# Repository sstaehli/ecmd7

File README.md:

# ECMD7

3-Phase Power Converter Hardware for Motor Drive Experiments.

Check the [documentation pages on gitlab.airhead.ch](https://gitlab-pages.airhead.ch/products/arnimatic/ecmd7/) or [documentation pages on GitHub](https://sstaehli.github.io/ecmd7/) for more info.

[](
https://github.com/sstaehli/ecmd7/actions/workflows/ci.yml
)

[](
https://gitlab.airhead.ch/products/arnimatic/ecmd7/-/pipelines
)

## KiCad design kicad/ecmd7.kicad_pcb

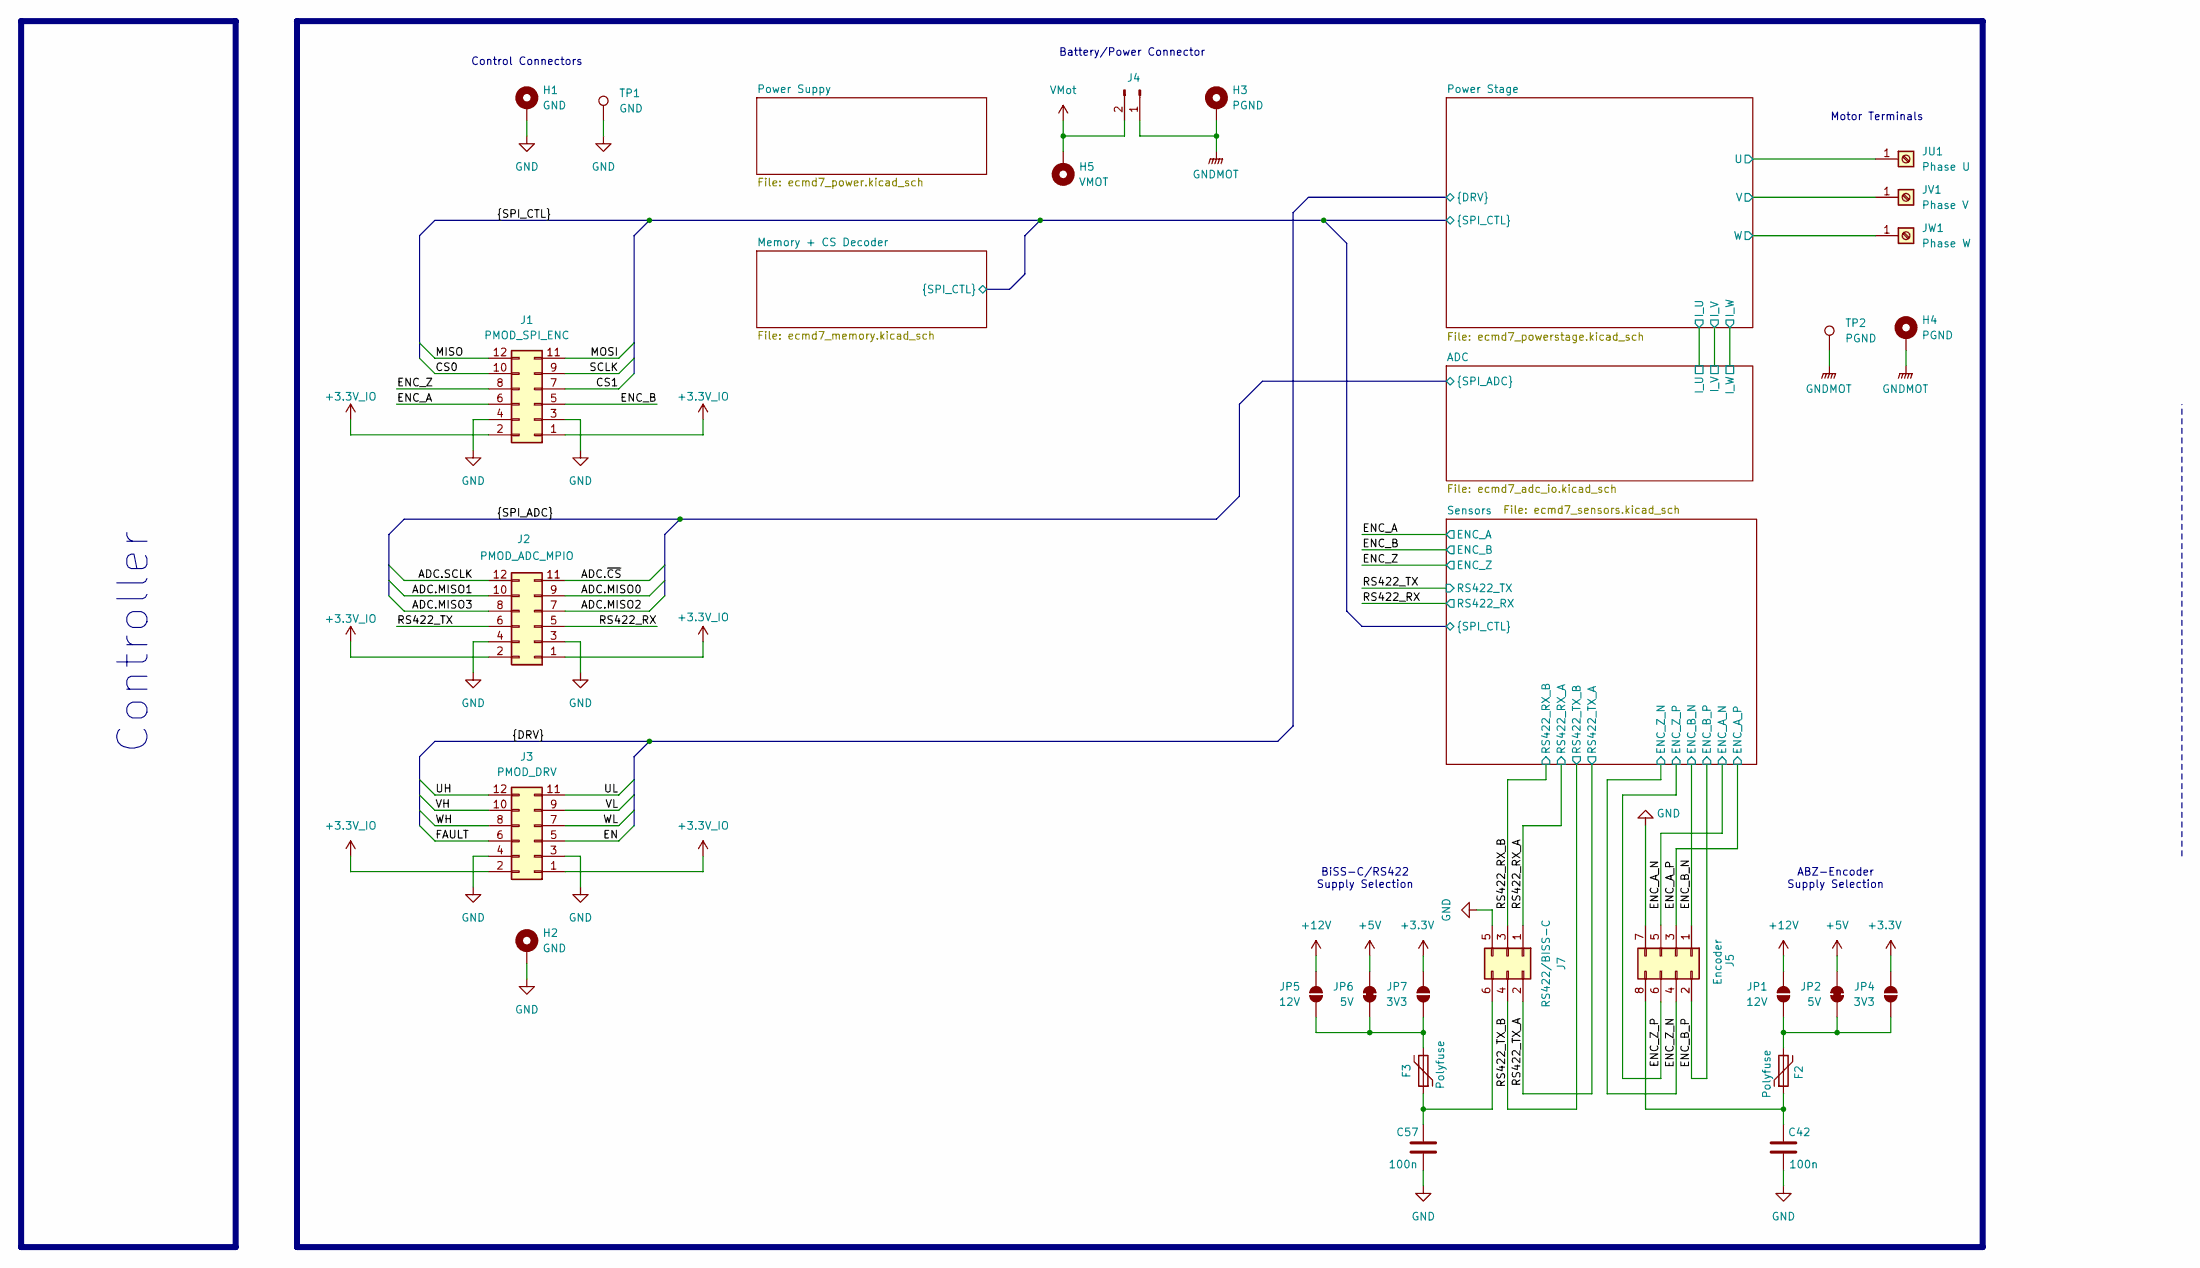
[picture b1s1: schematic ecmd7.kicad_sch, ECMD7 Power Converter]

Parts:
C42, C57: 100n; C_0805_2012Metric
F2, F3: Polyfuse; Fuse_0805_2012Metric
H1, H2: GND; MountingHole_3.2mm_M3_Pad_Via
H3, H4: PGND; MountingHole_3.2mm_M3_Pad_Via
H5: VMOT; MountingHole_3.2mm_M3_Pad_Via
J1: PMOD_SPI_ENC; PinHeader_2x06_P2.54mm_Horizontal
J2: PMOD_ADC_MPIO; PinHeader_2x06_P2.54mm_Horizontal
J3: PMOD_DRV; PinHeader_2x06_P2.54mm_Horizontal
J4: Conn_01x02_Socket; AMASS_XT60-M_1x02_P7.20mm_Vertical
J5: Encoder; PinHeader_2x04_P2.54mm_Vertical
J7: RS422/BISS-C; PinHeader_2x03_P2.54mm_Vertical
JP1, JP5: 12V; SolderJumper-2_P1.3mm_Open_RoundedPad1.0x1.5mm
JP2, JP6: 5V; SolderJumper-2_P1.3mm_Bridged_RoundedPad1.0x1.5mm
JP4, JP7: 3V3; SolderJumper-2_P1.3mm_Open_RoundedPad1.0x1.5mm
JU1: Phase U; MountingHole_3.2mm_M3_Pad_Via
JV1: Phase V; MountingHole_3.2mm_M3_Pad_Via
JW1: Phase W; MountingHole_3.2mm_M3_Pad_Via
TP1: GND; TestPoint_Loop_D2.50mm_Drill1.0mm
TP2: PGND; TestPoint_Loop_D2.50mm_Drill1.0mm

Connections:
+3.3V: JP4.2 (B), JP7.2 (B); also elsewhere on the board
+3.3V_IO: J1.1, J1.2, J2.1, J2.2, J3.1, J3.2; also elsewhere on the board
+5V: JP2.2 (B), JP6.2 (B); also elsewhere on the board
+12V: JP1.2 (B), JP5.2 (B); also elsewhere on the board
/ADC.MISO0: J2.9; also elsewhere on the board
/ADC.MISO1: J2.10; also elsewhere on the board
/ADC.MISO2: J2.7; also elsewhere on the board
/ADC.MISO3: J2.8; also elsewhere on the board
/ADC.SCLK: J2.12; also elsewhere on the board
/ADC.~CS: J2.11; also elsewhere on the board
/CS0: J1.10; also elsewhere on the board
/CS1: J1.7; also elsewhere on the board
/EN: J3.5; also elsewhere on the board
/ENC_A: J1.6; also elsewhere on the board
/ENC_A_N: J5.5; also elsewhere on the board
/ENC_A_P: J5.3; also elsewhere on the board
/ENC_B: J1.5; also elsewhere on the board
/ENC_B_N: J5.1; also elsewhere on the board
/ENC_B_P: J5.2; also elsewhere on the board
/ENC_Z: J1.8; also elsewhere on the board
/ENC_Z_N: J5.4; also elsewhere on the board
/ENC_Z_P: J5.6; also elsewhere on the board
/FAULT: J3.6; also elsewhere on the board
/MISO: J1.12; also elsewhere on the board
/MOSI: J1.11; also elsewhere on the board
/Power Stage/U: JU1.1; also elsewhere on the board
/Power Stage/V: JV1.1; also elsewhere on the board
/Power Stage/W: JW1.1; also elsewhere on the board
/RS422_RX: J2.5; also elsewhere on the board
/RS422_RX_A: J7.1; also elsewhere on the board
/RS422_RX_B: J7.3; also elsewhere on the board
/RS422_TX: J2.6; also elsewhere on the board
/RS422_TX_A: J7.2; also elsewhere on the board
/RS422_TX_B: J7.4; also elsewhere on the board
/SCLK: J1.9; also elsewhere on the board
/UH: J3.12; also elsewhere on the board
/UL: J3.11; also elsewhere on the board
/VH: J3.10; also elsewhere on the board
/VL: J3.9; also elsewhere on the board
/WH: J3.8; also elsewhere on the board
/WL: J3.7; also elsewhere on the board
GND: C42.2, C57.2, H1.1, H2.1, J1.3, J1.4, J2.3, J2.4, J3.3, J3.4, J5.7, J7.5, TP1.1; also elsewhere on the board
GNDMOT: H3.1, H4.1, J4.1, TP2.1; also elsewhere on the board
unnamed: C42.1, F2.1, J5.8
unnamed: C57.1, F3.1, J7.6
unnamed: F2.2, JP1.1 (A), JP2.1 (A), JP4.1 (A)
unnamed: F3.2, JP5.1 (A), JP6.1 (A), JP7.1 (A)
VMot: H5.1, J4.2; also elsewhere on the board

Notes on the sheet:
ABZ-Encoder Supply Selection
Controller
Battery/Power Connector
Motor Terminals
Control Connectors
BiSS-C/RS422 Supply Selection

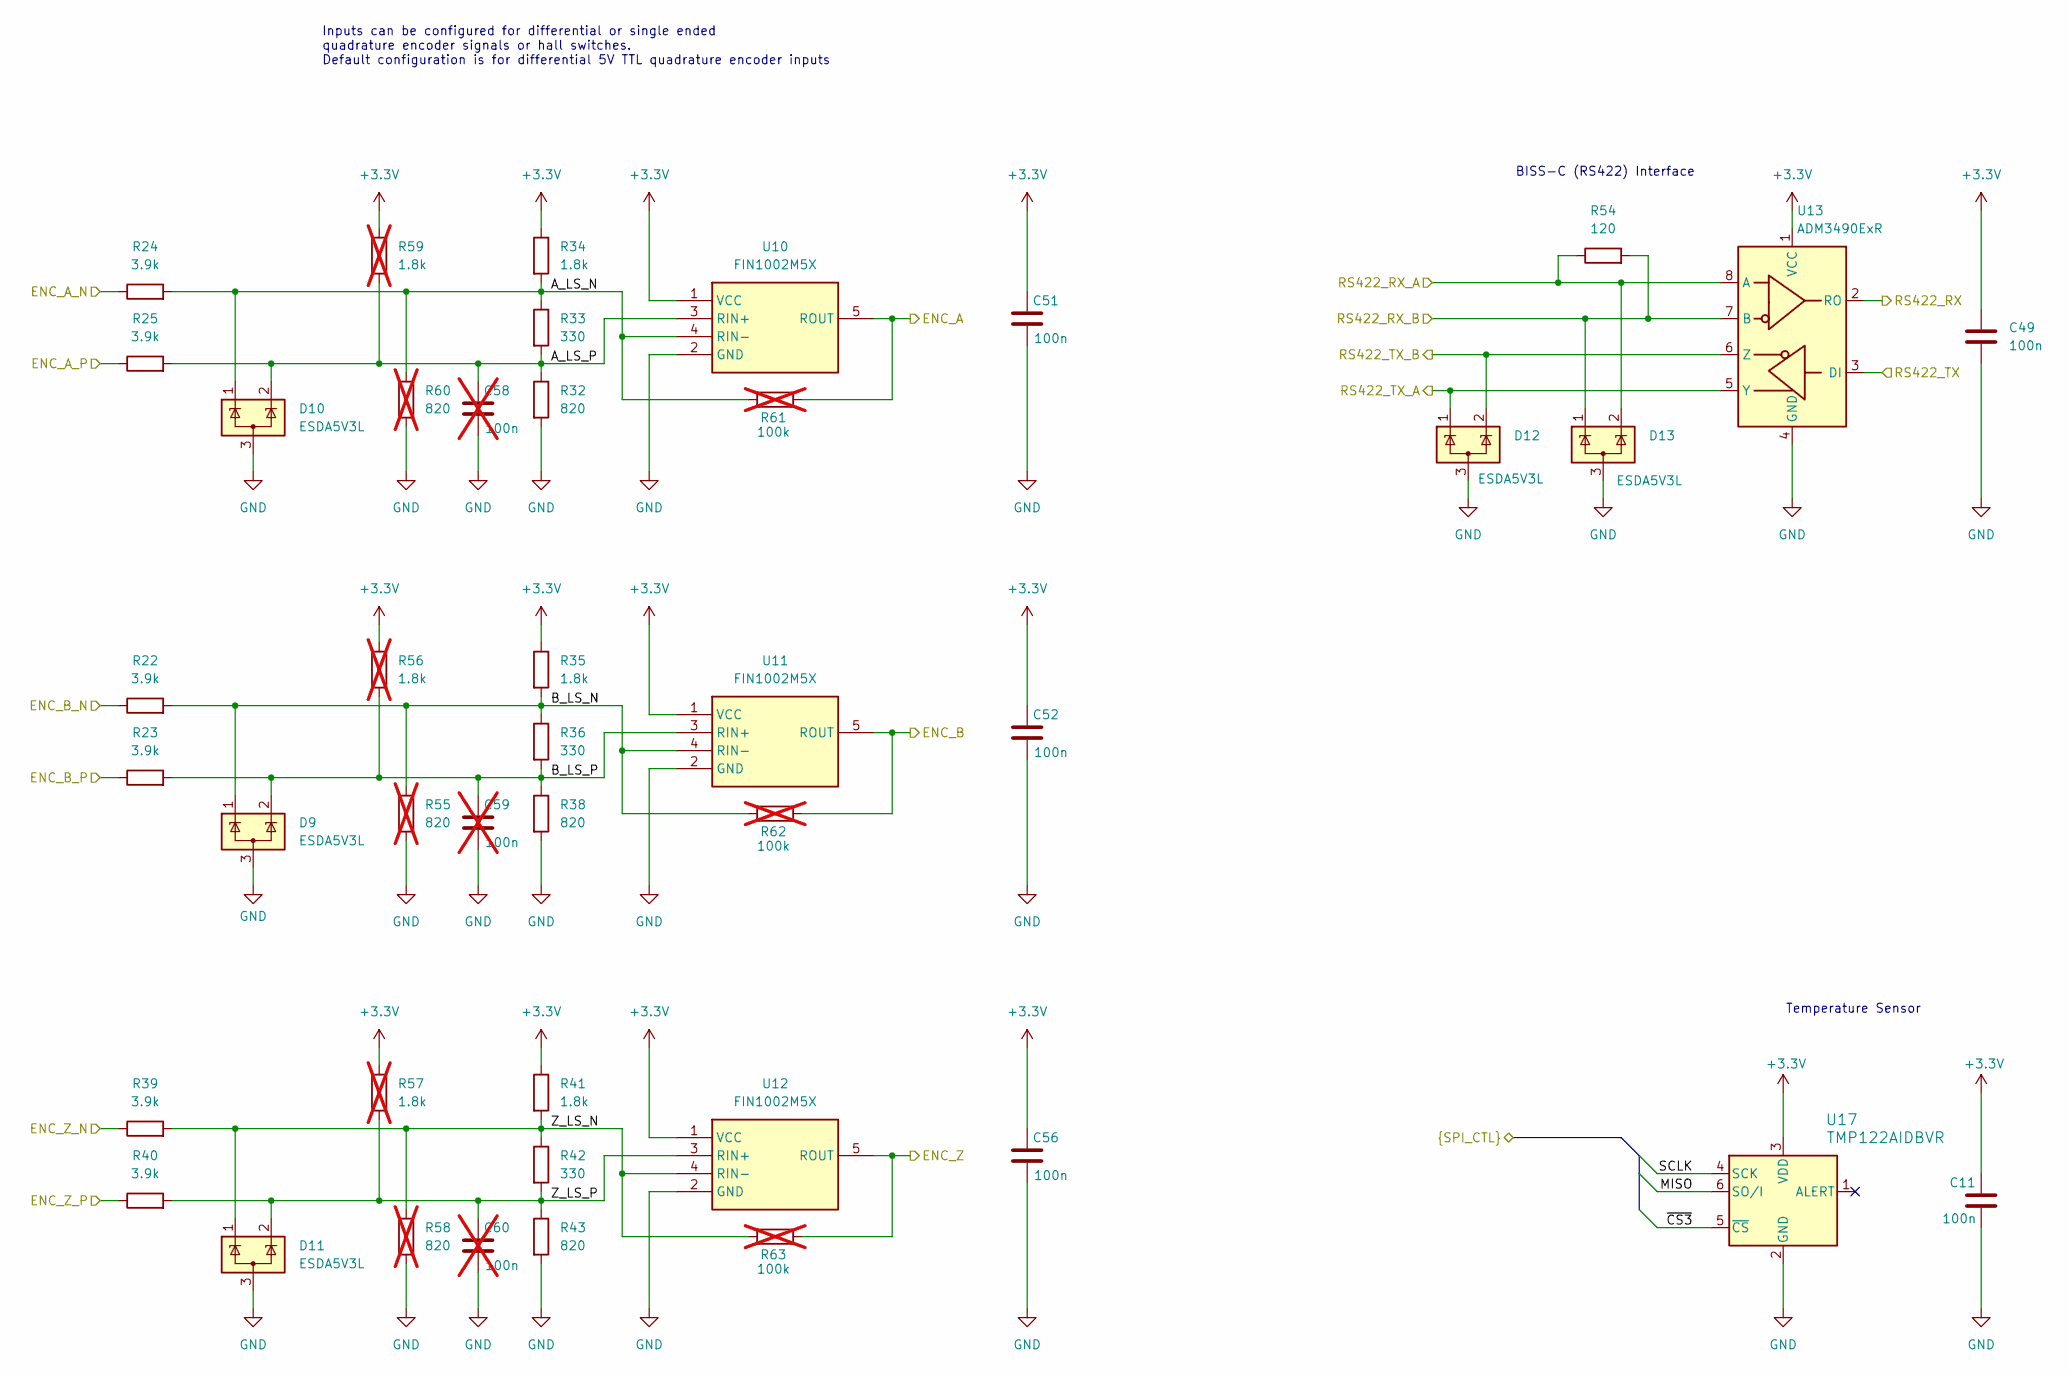
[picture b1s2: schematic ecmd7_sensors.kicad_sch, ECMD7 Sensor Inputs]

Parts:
C11, C51, C52, C56: 100n; C_0805_2012Metric
C49: 100n; C_0603_1608Metric; Mouser Part Number 581-06035C104KAT2A
C58, C59, C60: 100n; C_0805_2012Metric; not fitted
D9, D10, D11, D12, D13: ESDA5V3L; SOT-23-3; Mouser Part Number 511-ESDA5V3L
R22, R23, R24, R25, R39, R40: 3.9k; R_0805_2012Metric
R32, R38, R43: 820; R_0805_2012Metric
R33, R36, R42: 330; R_0805_2012Metric
R34, R35, R41: 1.8k; R_0805_2012Metric
R54: 120; R_0805_2012Metric
R55, R58, R60: 820; R_0805_2012Metric; not fitted
R56, R57, R59: 1.8k; R_0805_2012Metric; not fitted
R61, R62, R63: 100k; R_0805_2012Metric; not fitted
U10, U11, U12: FIN1002M5X; SOT-23-5; Mouser Part Number 512-FIN1002M5X
U13: ADM3490ExR; SOIC-8_3.9x4.9mm_P1.27mm; Mouser Part Number 584-ADM3490EARZ
U17: TMP122AIDBVR; DBV6

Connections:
+3.3V: C11.1, C49.1, C51.1, C52.1, C56.1, R34.1, R35.1, R41.1, R56.1, R57.1, R59.1, U10.1 (VCC), U11.1 (VCC), U12.1 (VCC), U13.1 (VCC), U17.3 (VDD); also elsewhere on the board
/ENC_A: R61.2, U10.5 (ROUT); also elsewhere on the board
/ENC_A_N: R24.1; also elsewhere on the board
/ENC_A_P: R25.1; also elsewhere on the board
/ENC_B: R62.2, U11.5 (ROUT); also elsewhere on the board
/ENC_B_N: R22.1; also elsewhere on the board
/ENC_B_P: R23.1; also elsewhere on the board
/ENC_Z: R63.2, U12.5 (ROUT); also elsewhere on the board
/ENC_Z_N: R39.1; also elsewhere on the board
/ENC_Z_P: R40.1; also elsewhere on the board
/MISO: U17.6 (SO/I); also elsewhere on the board
/RS422_RX: U13.2 (RO); also elsewhere on the board
/RS422_RX_A: D13.2 (K), R54.1, U13.8 (A); also elsewhere on the board
/RS422_RX_B: D13.1 (K), R54.2, U13.7 (B); also elsewhere on the board
/RS422_TX: U13.3 (DI); also elsewhere on the board
/RS422_TX_A: D12.1 (K), U13.5 (Y); also elsewhere on the board
/RS422_TX_B: D12.2 (K), U13.6 (Z); also elsewhere on the board
/SCLK: U17.4 (SCK); also elsewhere on the board
/Sensors/A_LS_N: D10.1 (K), R24.2, R33.1, R34.2, R60.1, R61.1, U10.4 (RIN-)
/Sensors/A_LS_P: C58.1, D10.2 (K), R25.2, R32.1, R33.2, R59.2, U10.3 (RIN+)
/Sensors/B_LS_N: D9.1 (K), R22.2, R35.2, R36.1, R55.1, R62.1, U11.4 (RIN-)
/Sensors/B_LS_P: C59.1, D9.2 (K), R23.2, R36.2, R38.1, R56.2, U11.3 (RIN+)
/Sensors/Z_LS_N: D11.1 (K), R39.2, R41.2, R42.1, R58.1, R63.1, U12.4 (RIN-)
/Sensors/Z_LS_P: C60.1, D11.2 (K), R40.2, R42.2, R43.1, R57.2, U12.3 (RIN+)
/~CS3: U17.5 (~CS); also elsewhere on the board
GND: C11.2, C49.2, C51.2, C52.2, C56.2, C58.2, C59.2, C60.2, D9.3 (A), D10.3 (A), D11.3 (A), D12.3 (A), D13.3 (A), R32.2, R38.2, R43.2, R55.2, R58.2, R60.2, U10.2 (GND), U11.2 (GND), U12.2 (GND), U13.4 (GND), U17.2 (GND); also elsewhere on the board

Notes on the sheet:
Temperature Sensor
Inputs can be configured for differential or single ended quadrature encoder signals or hall switches. Default configuration is for differential 5V TTL quadrature encoder inputs
BISS-C (RS422) Interface

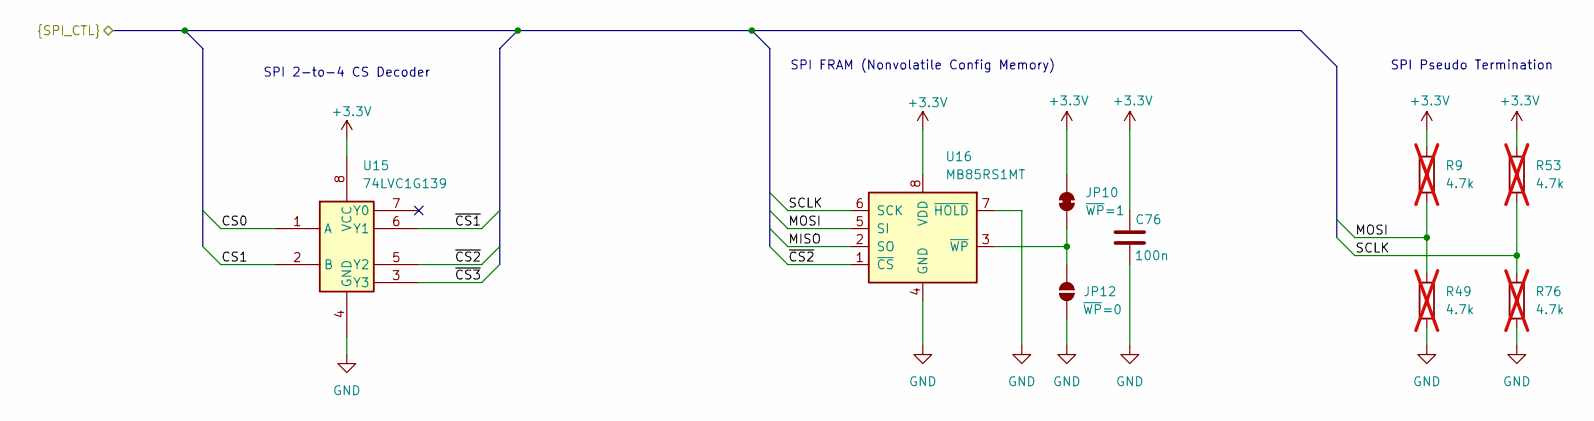
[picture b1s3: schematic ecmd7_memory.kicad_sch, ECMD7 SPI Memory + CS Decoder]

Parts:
C76: 100n; C_0805_2012Metric
JP10: ~{WP}=1; SolderJumper-2_P1.3mm_Bridged_RoundedPad1.0x1.5mm
JP12: ~{WP}=0; SolderJumper-2_P1.3mm_Open_RoundedPad1.0x1.5mm
R9, R49, R53, R76: 4.7k; R_0805_2012Metric; not fitted
U15: 74LVC1G139; SSOP-8_2.95x2.8mm_P0.65mm
U16: MB85RS1MT; SOP-8_3.76x4.96mm_P1.27mm

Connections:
+3.3V: C76.1, JP10.2 (B), R9.1, R53.1, U15.8 (VCC), U16.8 (VDD); also elsewhere on the board
/CS0: U15.1 (A); also elsewhere on the board
/CS1: U15.2 (B); also elsewhere on the board
/MISO: U16.2 (SO); also elsewhere on the board
/MOSI: R9.2, R49.1, U16.5 (SI); also elsewhere on the board
/SCLK: R53.2, R76.1, U16.6 (SCK); also elsewhere on the board
/~CS1: U15.6 (Y1); also elsewhere on the board
/~CS2: U15.5 (Y2), U16.1 (~CS)
/~CS3: U15.3 (Y3); also elsewhere on the board
GND: C76.2, JP12.1 (A), R49.2, R76.2, U15.4 (GND), U16.4 (GND), U16.7 (~HOLD); also elsewhere on the board
unnamed: JP10.1 (A), JP12.2 (B), U16.3 (~WP)

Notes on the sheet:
SPI 2-to-4 CS Decoder
SPI Pseudo Termination
SPI FRAM (Nonvolatile Config Memory)

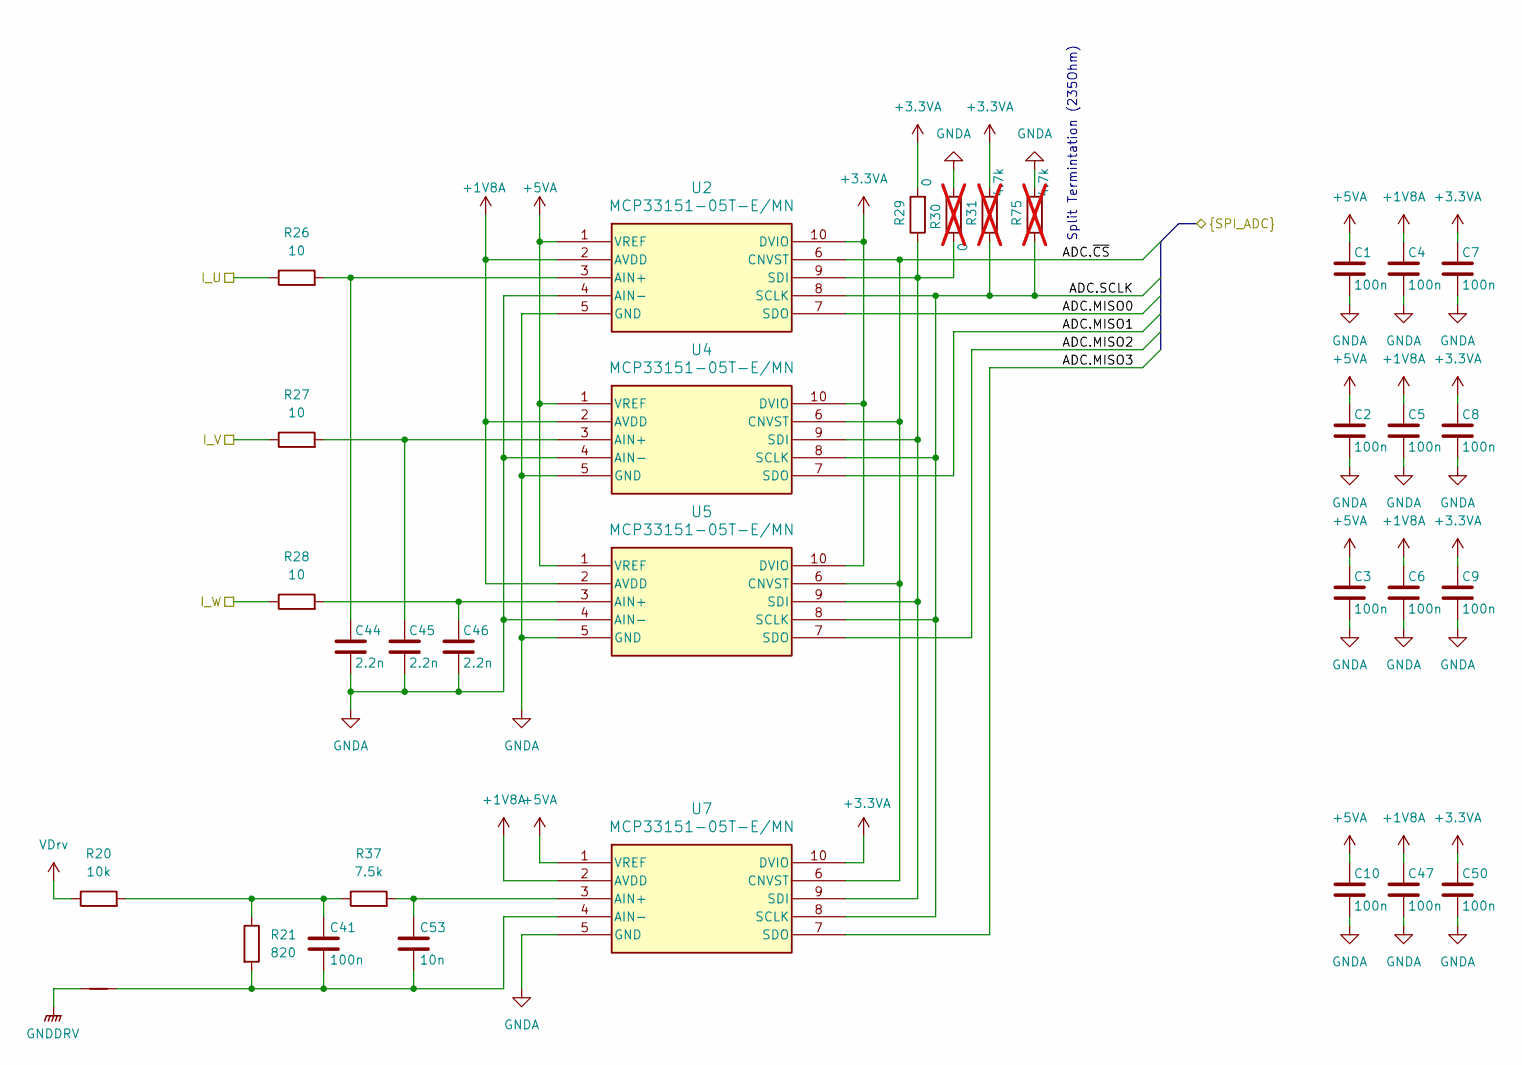
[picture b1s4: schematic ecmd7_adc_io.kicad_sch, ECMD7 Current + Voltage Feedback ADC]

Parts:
C1, C2, C3, C4, C5, C6, C7, C8, C9, C10, C41, C47, C50: 100n; C_0805_2012Metric
C44, C45, C46: 2.2n; C_0805_2012Metric
C53: 10n; C_0805_2012Metric
NTP2G3: NetTie_2; NetTie-2_SMD_Pad0.5mm
R20: 10k; R_0805_2012Metric
R21: 820; R_0805_2012Metric
R26, R27, R28: 10; R_0805_2012Metric
R29: 0; R_0805_2012Metric
R30: 0; R_0805_2012Metric; not fitted
R31, R75: 4.7k; R_0805_2012Metric; not fitted
R37: 7.5k; R_0805_2012Metric
U2, U4, U5, U7: MCP33151-05T-E/MN; TDFN10_MN_MCH

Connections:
+1V8A: C4.1, C5.1, C6.1, C47.1, U2.2 (AVDD), U4.2 (AVDD), U5.2 (AVDD), U7.2 (AVDD); also elsewhere on the board
+3.3VA: C7.1, C8.1, C9.1, C50.1, R29.2, R31.2, U2.10 (DVIO), U4.10 (DVIO), U5.10 (DVIO), U7.10 (DVIO); also elsewhere on the board
+5VA: C1.1, C2.1, C3.1, C10.1, U2.1 (VREF), U4.1 (VREF), U5.1 (VREF), U7.1 (VREF); also elsewhere on the board
/ADC.MISO0: U2.7 (SDO); also elsewhere on the board
/ADC.MISO1: U4.7 (SDO); also elsewhere on the board
/ADC.MISO2: U5.7 (SDO); also elsewhere on the board
/ADC.MISO3: U7.7 (SDO); also elsewhere on the board
/ADC.SCLK: R31.1, R75.1, U2.8 (SCLK), U4.8 (SCLK), U5.8 (SCLK), U7.8 (SCLK); also elsewhere on the board
/ADC.~CS: U2.6 (CNVST), U4.6 (CNVST), U5.6 (CNVST), U7.6 (CNVST); also elsewhere on the board
/ADC/I_U: R26.1; also elsewhere on the board
/ADC/I_V: R27.1; also elsewhere on the board
/ADC/I_W: R28.1; also elsewhere on the board
GNDA: C1.2, C2.2, C3.2, C4.2, C5.2, C6.2, C7.2, C8.2, C9.2, C10.2, C44.2, C45.2, C46.2, C47.2, C50.2, R30.1, R75.2, U2.4 (AIN-), U2.5 (GND), U4.4 (AIN-), U4.5 (GND), U5.4 (AIN-), U5.5 (GND), U7.5 (GND); also elsewhere on the board
GNDDRV: NTP2G3.2; also elsewhere on the board
unnamed: C41.1, R20.2, R21.1, R37.1
unnamed: C44.1, R26.2, U2.3 (AIN+)
unnamed: R29.1, R30.2, U2.9 (SDI), U4.9 (SDI), U5.9 (SDI), U7.9 (SDI)
unnamed: C45.1, R27.2, U4.3 (AIN+)
unnamed: C46.1, R28.2, U5.3 (AIN+)
unnamed: C53.1, R37.2, U7.3 (AIN+)
unnamed: C41.2, C53.2, NTP2G3.1, R21.2, U7.4 (AIN-)
VDrv: R20.1; also elsewhere on the board

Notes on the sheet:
Split Termintation (235Ohm)

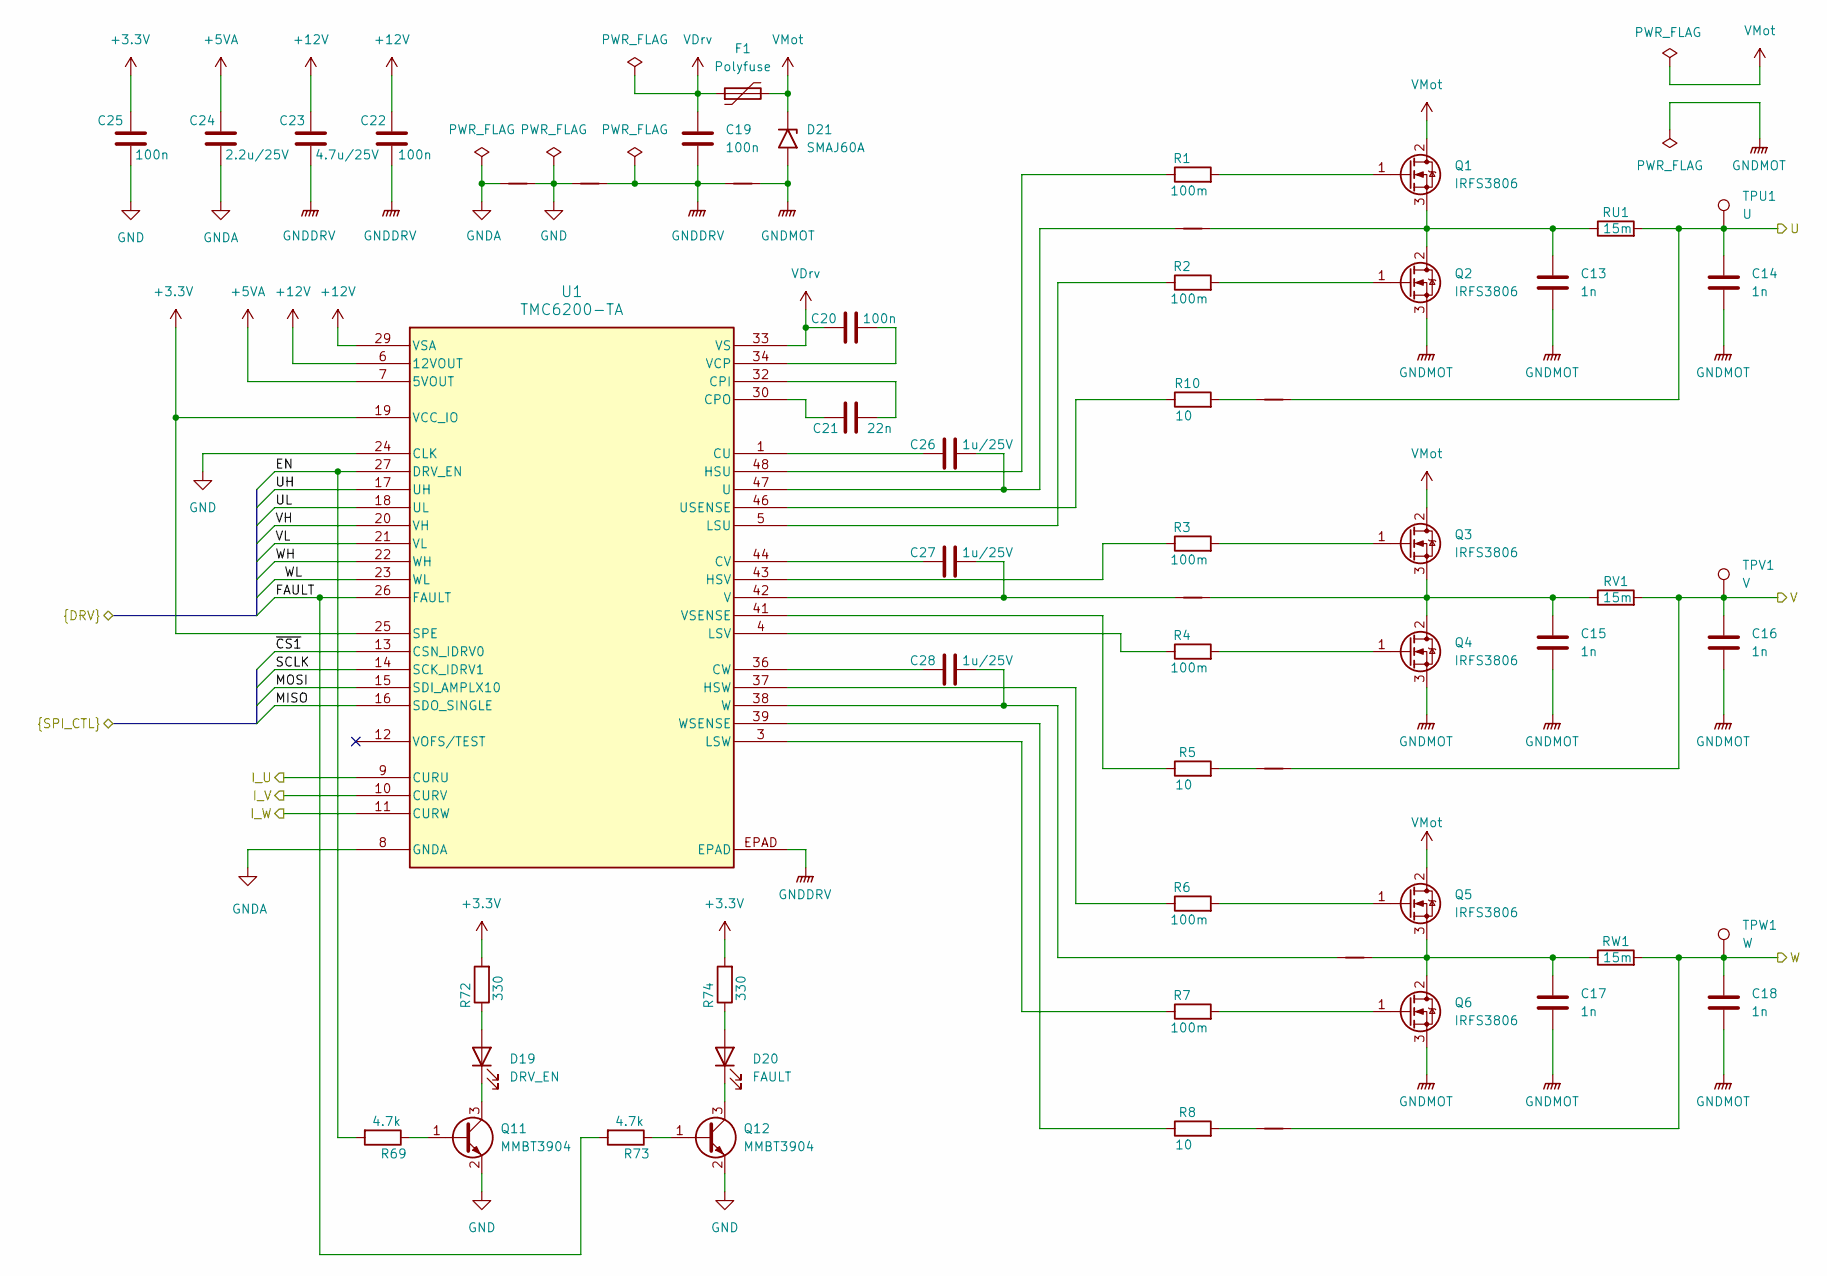
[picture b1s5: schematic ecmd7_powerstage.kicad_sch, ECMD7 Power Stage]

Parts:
C13, C14, C15, C16, C17, C18: 1n; C_0805_2012Metric
C19, C20, C22, C25: 100n; C_0805_2012Metric
C21: 22n; C_0805_2012Metric
C23: 4.7u/25V; C_0805_2012Metric
C24: 2.2u/25V; C_0805_2012Metric
C26, C27, C28: 1u/25V; C_0805_2012Metric
D19: DRV_EN; D_0805_2012Metric
D20: FAULT; D_0805_2012Metric
D21: SMAJ60A; D_SMA; Mouser Part Number 576-SMAJ60A
F1: Polyfuse; Fuse_0805_2012Metric
NTP2G1, NTP2G4: NetTie_2; NetTie-2_SMD_Pad2.0mm
NTP2G2: NetTie_2; NetTie-2_SMD_Pad0.5mm
NTPU1: NetTie_2; NetTie-2_SMD_Pad0.5mm
NTPV1: NetTie_2; NetTie-2_SMD_Pad0.5mm
NTPW1: NetTie_2; NetTie-2_SMD_Pad0.5mm
NTSU1: NetTie_2; NetTie-2_SMD_Pad0.5mm
NTSV1: NetTie_2; NetTie-2_SMD_Pad0.5mm
NTSW1: NetTie_2; NetTie-2_SMD_Pad0.5mm
Q1, Q2, Q3, Q4, Q5, Q6: IRFS3806; TO-263-2
Q11, Q12: MMBT3904; SOT-23
R1, R2, R3, R4, R6, R7: 100m; R_0805_2012Metric
R5, R8, R10: 10; R_0805_2012Metric
R69, R73: 4.7k; R_0805_2012Metric
R72, R74: 330; R_0805_2012Metric
RU1: 15m; R_0612_1632Metric
RV1: 15m; R_0612_1632Metric
RW1: 15m; R_0612_1632Metric
TPU1: U; TestPoint_Loop_D2.50mm_Drill1.0mm
TPV1: V; TestPoint_Loop_D2.50mm_Drill1.0mm
TPW1: W; TestPoint_Loop_D2.50mm_Drill1.0mm
U1: TMC6200-TA; eTQFP48_9x9_TRI

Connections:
+3.3V: C25.1, R72.2, R74.2, U1.19 (VCC_IO), U1.25 (SPE); also elsewhere on the board
+5VA: C24.1, U1.7 (5VOUT); also elsewhere on the board
+12V: C22.1, C23.1, U1.6 (12VOUT), U1.29 (VSA); also elsewhere on the board
/ADC/I_U: U1.9 (CURU); also elsewhere on the board
/ADC/I_V: U1.10 (CURV); also elsewhere on the board
/ADC/I_W: U1.11 (CURW); also elsewhere on the board
/EN: R69.2, U1.27 (DRV_EN); also elsewhere on the board
/FAULT: R73.2, U1.26 (FAULT); also elsewhere on the board
/MISO: U1.16 (SDO_SINGLE); also elsewhere on the board
/MOSI: U1.15 (SDI_AMPLX10); also elsewhere on the board
/Power Stage/U: C14.1, NTSU1.1, RU1.2, TPU1.1; also elsewhere on the board
/Power Stage/V: C16.1, NTSV1.2, RV1.2, TPV1.1; also elsewhere on the board
/Power Stage/W: C18.1, NTSW1.2, RW1.2, TPW1.1; also elsewhere on the board
/SCLK: U1.14 (SCK_IDRV1); also elsewhere on the board
/UH: U1.17 (UH); also elsewhere on the board
/UL: U1.18 (UL); also elsewhere on the board
/VH: U1.20 (VH); also elsewhere on the board
/VL: U1.21 (VL); also elsewhere on the board
/WH: U1.22 (WH); also elsewhere on the board
/WL: U1.23 (WL); also elsewhere on the board
/~CS1: U1.13 (CSN_IDRV0); also elsewhere on the board
GND: C25.2, NTP2G1.2, NTP2G2.1, Q11.2 (E), Q12.2 (E), U1.24 (CLK); also elsewhere on the board
GNDA: C24.2, NTP2G2.2, U1.8 (GNDA); also elsewhere on the board
GNDDRV: C19.2, C22.2, C23.2, NTP2G1.1, NTP2G4.2, U1.EPAD; also elsewhere on the board
GNDMOT: C13.2, C14.2, C15.2, C16.2, C17.2, C18.2, D21.2 (A2), NTP2G4.1, Q2.3 (S), Q4.3 (S), Q6.3 (S); also elsewhere on the board
unnamed: D19.2 (A), R72.1
unnamed: D19.1 (K), Q11.3 (C)
unnamed: D20.2 (A), R74.1
unnamed: D20.1 (K), Q12.3 (C)
unnamed: NTSU1.2, R10.2
unnamed: NTSV1.1, R5.2
unnamed: NTSW1.1, R8.2
unnamed: Q1.1 (G), R1.2
unnamed: C13.1, NTPU1.1, Q1.3 (S), Q2.2 (D), RU1.1
unnamed: Q2.1 (G), R2.2
unnamed: Q3.1 (G), R3.2
unnamed: C15.1, NTPV1.1, Q3.3 (S), Q4.2 (D), RV1.1
unnamed: Q4.1 (G), R4.2
unnamed: Q5.1 (G), R6.2
unnamed: C17.1, NTPW1.1, Q5.3 (S), Q6.2 (D), RW1.1
unnamed: Q6.1 (G), R7.2
unnamed: Q11.1 (B), R69.1
unnamed: Q12.1 (B), R73.1
unnamed: C21.1, U1.32 (CPI)
unnamed: C21.2, U1.30 (CPO)
unnamed: C26.2, U1.1 (CU)
unnamed: C27.2, U1.44 (CV)
unnamed: C28.2, U1.36 (CW)
unnamed: R1.1, U1.48 (HSU)
unnamed: R3.1, U1.43 (HSV)
unnamed: R6.1, U1.37 (HSW)
unnamed: R2.1, U1.5 (LSU)
unnamed: R4.1, U1.4 (LSV)
unnamed: R7.1, U1.3 (LSW)
unnamed: C26.1, NTPU1.2, U1.47 (U)
unnamed: R10.1, U1.46 (USENSE)
unnamed: C27.1, NTPV1.2, U1.42 (V)
unnamed: C20.1, U1.34 (VCP)
unnamed: R5.1, U1.41 (VSENSE)
unnamed: C28.1, NTPW1.2, U1.38 (W)
unnamed: R8.1, U1.39 (WSENSE)
VDrv: C19.1, C20.2, F1.1, U1.33 (VS); also elsewhere on the board
VMot: D21.1 (A1), F1.2, Q1.2 (D), Q3.2 (D), Q5.2 (D); also elsewhere on the board

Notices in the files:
kicad/ecmd7.kicad_pcb:
©2025 S. Stähli
